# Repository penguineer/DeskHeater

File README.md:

# Desk Heater

> Low-power heated desktop for reducing conductive heat loss while working in a cool room.

This project adds a thin 24 V carbon heating film underneath a bamboo desktop. The goal is not to make the desk feel hot, but to keep the work surface close enough to room/body-neutral temperature that it no longer cools hands and forearms during long work sessions in winter.

The controller is based on an ESP8266 (ESP-12E) and provides:

- temperature monitoring with multiple NTC sensors
- hardware over-temperature protection independent of the ESP
- current, voltage, power and energy measurement
- slow duty-cycle control of the approximately 60 W heating film
- UART and Wi-Fi connectivity for monitoring and future controls

The KiCad design for the controller is in [`Controller/`](Controller/).

## Status

Work in progress. The electrical and mechanical design is currently being prototyped and characterized.

## License

This work is licensed under a [Creative Commons Attribution-ShareAlike 4.0 International License](http://creativecommons.org/licenses/by-sa/4.0/).

BY: Stefan Haun (mail@tuxathome.de)

See [LICENSE.txt](LICENSE.txt) for details.

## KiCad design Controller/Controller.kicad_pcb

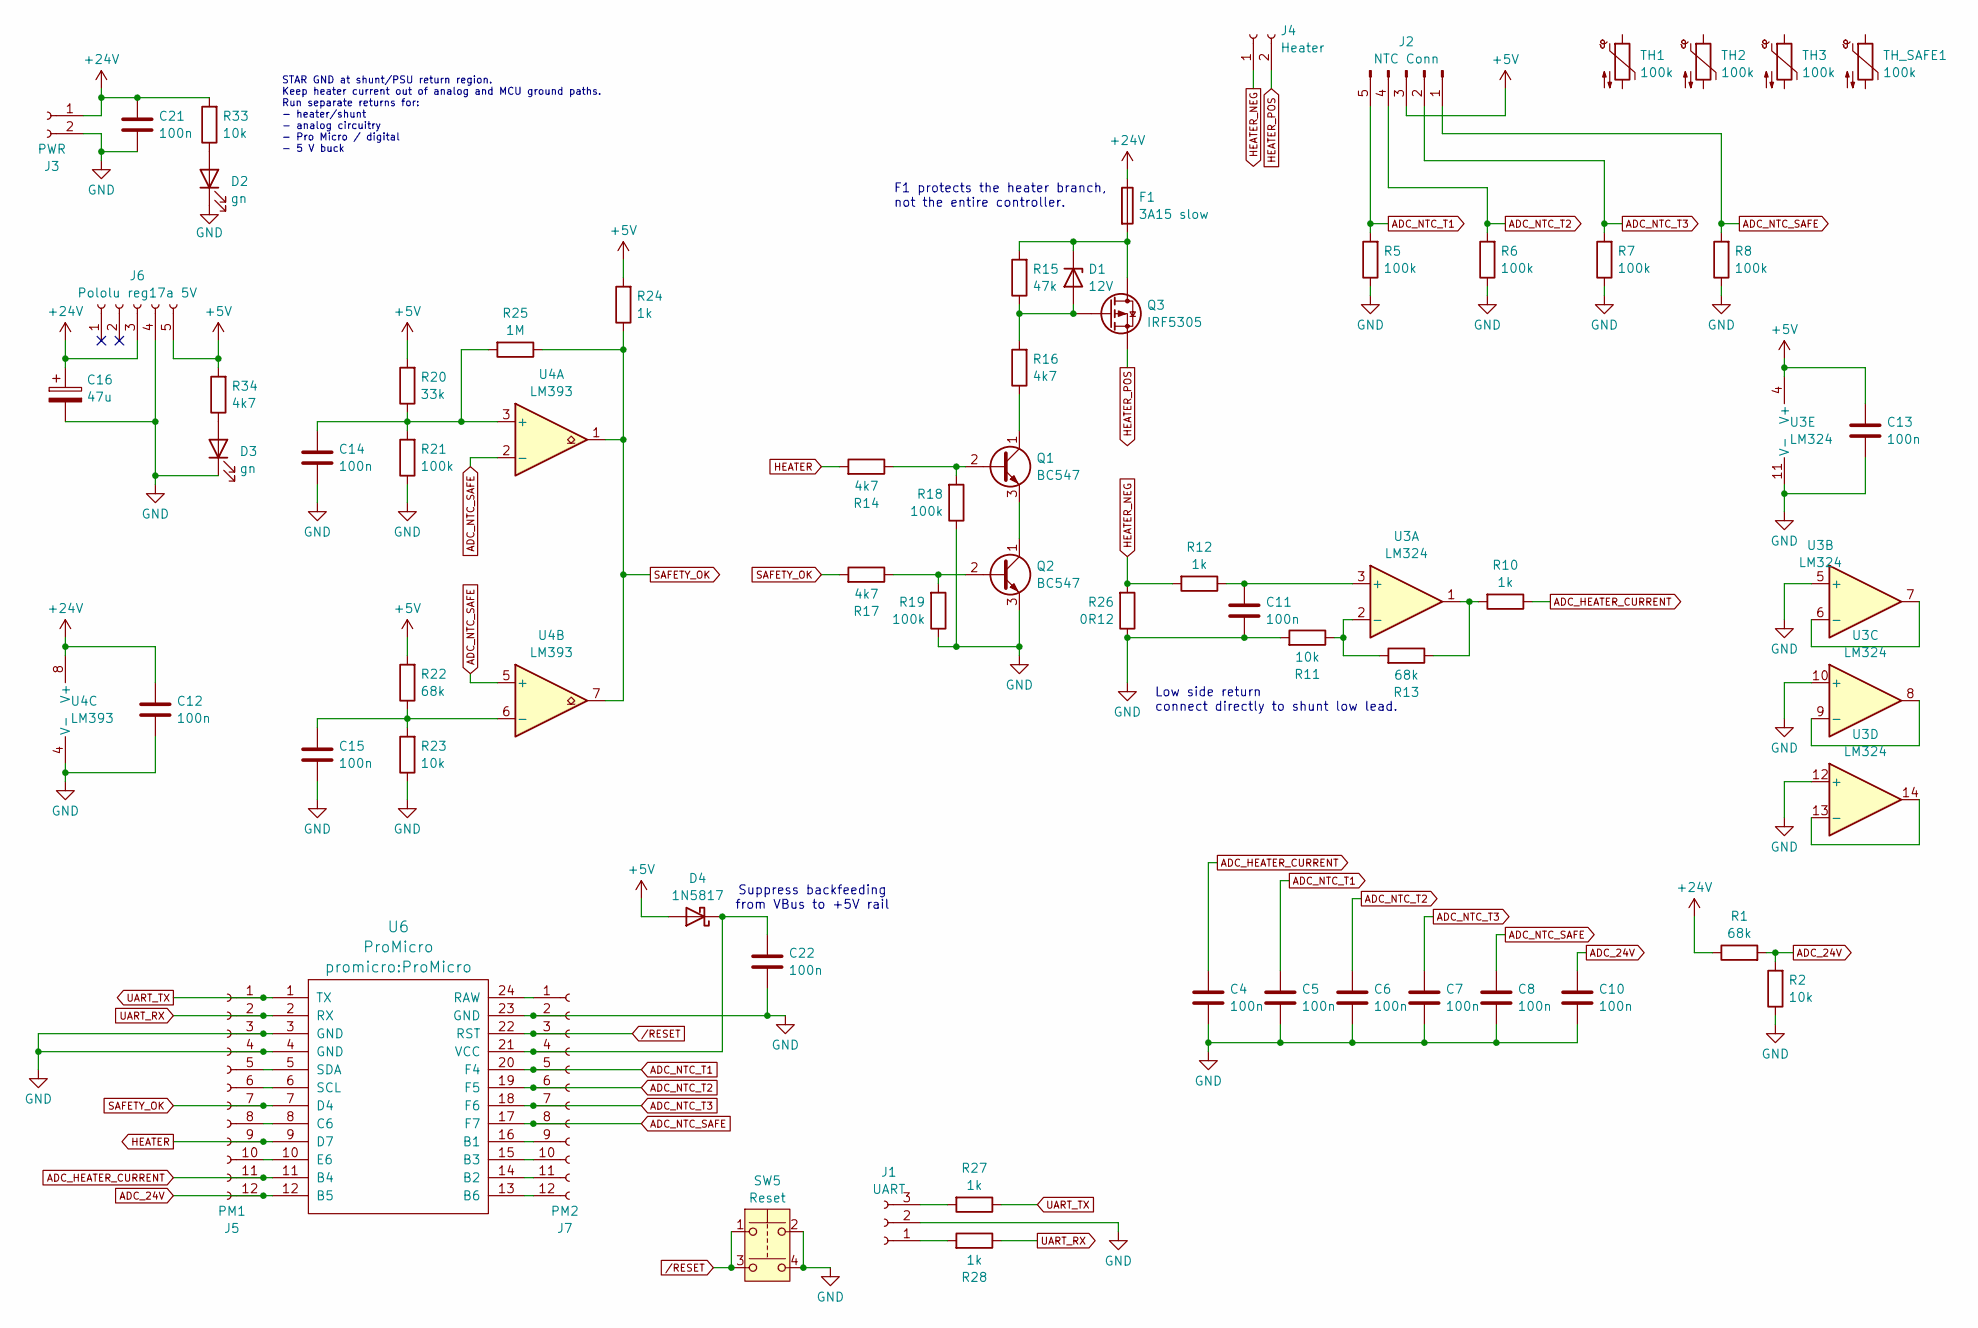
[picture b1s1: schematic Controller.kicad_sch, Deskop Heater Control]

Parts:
C4, C5, C6, C7, C8, C10, C11, C12, C13, C14, C15, C21, C22: 100n; C_Disc_D4.3mm_W1.9mm_P5.00mm
C16: 47u; CP_Radial_D6.3mm_P2.50mm
D1: 12V; D_DO-41_SOD81_P7.62mm_Horizontal
D2, D3: gn; LED_D3.0mm
D4: 1N5817; D_DO-41_SOD81_P10.16mm_Horizontal
F1: 3A15 slow; Fuseholder_Cylinder-5x20mm_Stelvio-Kontek_PTF78_Horizontal_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
J1: UART; PinHeader_1x03_P2.54mm_Vertical
J2: NTC Conn; JST_EH_B5B-EH-A_1x05_P2.50mm_Vertical
J3: PWR; JST_NV_B02P-NV_1x02_P5.00mm_Vertical
J4: Heater; JST_NV_B02P-NV_1x02_P5.00mm_Vertical
J5: PM1; PinSocket_1x12_P2.54mm_Vertical
J6: Pololu reg17a 5V; PinHeader_1x05_P2.54mm_Vertical
J7: PM2; PinSocket_1x12_P2.54mm_Vertical
Q1, Q2: BC547; TO-92_Inline
Q3: IRF5305; TO-220-3_Vertical
R1, R13, R22: 68k; R_Axial_DIN0207_L6.3mm_D2.5mm_P7.62mm_Horizontal
R2, R11, R23, R33: 10k; R_Axial_DIN0207_L6.3mm_D2.5mm_P7.62mm_Horizontal
R5, R6, R7, R8, R18, R19, R21: 100k; R_Axial_DIN0207_L6.3mm_D2.5mm_P7.62mm_Horizontal
R10, R12, R24, R27, R28: 1k; R_Axial_DIN0207_L6.3mm_D2.5mm_P7.62mm_Horizontal
R14, R16, R17, R34: 4k7; R_Axial_DIN0207_L6.3mm_D2.5mm_P7.62mm_Horizontal
R15: 47k; R_Axial_DIN0207_L6.3mm_D2.5mm_P7.62mm_Horizontal
R20: 33k; R_Axial_DIN0207_L6.3mm_D2.5mm_P7.62mm_Horizontal
R25: 1M; R_Axial_DIN0207_L6.3mm_D2.5mm_P7.62mm_Horizontal
R26: 0R12; R_Axial_DIN0614_L14.3mm_D5.7mm_P15.24mm_Horizontal
SW5: Reset; SW_DIP_SPSTx02_Slide_6.7x6.64mm_W7.62mm_P2.54mm_LowProfile
TH1, TH2, TH3: 100k; LQFP-100_14x14mm_P0.5mm
TH_SAFE1: 100k; LQFP-100_14x14mm_P0.5mm
U3: LM324; DIP-14_W7.62mm_LongPads
U4: LM393; DIP-8_W7.62mm_LongPads
U6: ProMicro

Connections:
+5V: C13.1, D4.2 (A), J2.3, J6.5, R20.2, R22.2, R24.2, R34.2, U3.4 (V+)
+24V: C12.1, C16.1, C21.1, F1.1, J3.1, J6.3, R1.1, R33.2, U4.8 (V+)
ADC_24V: C10.1, J5.12, R1.2, R2.2, U6.12 (B5)
ADC_HEATER_CURRENT: C4.1, J5.11, R10.1, U6.11 (B4)
ADC_NTC_SAFE: C8.1, J2.1, J7.8, R8.2, U4.2 (-), U4.5 (+), U6.17 (F7)
ADC_NTC_T1: C5.1, J2.5, J7.5, R5.2, U6.20 (F4)
ADC_NTC_T2: C6.1, J2.4, J7.6, R6.2, U6.19 (F5)
ADC_NTC_T3: C7.1, J2.2, J7.7, R7.2, U6.18 (F6)
GND: C4.2, C5.2, C6.2, C7.2, C8.2, C10.2, C11.2, C12.2, C13.2, C14.2, C15.2, C16.2, C21.2, C22.2, D2.1 (K), D3.1 (K), J1.2, J3.2, J5.3, J5.4, J6.4, J7.2, Q2.3 (E), R2.1, R5.1, R6.1, R7.1, R8.1, R11.2, R18.1, R19.1, R21.1, R23.1, R26.1, SW5.2, SW5.4, U3.5 (+), U3.10 (+), U3.11 (V-), U3.12 (+), U4.4 (V-), U6.3 (GND), U6.4 (GND), U6.23 (GND)
HEATER: J5.9, R14.2, U6.9 (D7)
HEATER_NEG: J4.1, R12.2, R26.2
HEATER_POS: J4.2, Q3.3 (S)
unnamed: D1.2 (A), Q3.1 (G), R15.1, R16.2
unnamed: D1.1 (K), F1.2, Q3.2 (D), R15.2
unnamed: D2.2 (A), R33.1
unnamed: D3.2 (A), R34.1
unnamed: C22.1, D4.1 (K), J7.4, U6.21 (VCC)
unnamed: J1.1, R28.2
unnamed: J1.3, R27.2
unnamed: J5.5, U6.5 (SDA)
unnamed: J5.6, U6.6 (SCL)
unnamed: J5.8, U6.8 (C6)
unnamed: J5.10, U6.10 (E6)
unnamed: J7.1, U6.24 (RAW)
unnamed: J7.9, U6.16 (B1)
unnamed: J7.10, U6.15 (B3)
unnamed: J7.11, U6.14 (B2)
unnamed: J7.12, U6.13 (B6)
unnamed: Q1.2 (B), R14.1, R18.2
unnamed: Q1.1 (C), R16.1
unnamed: Q1.3 (E), Q2.1 (C)
unnamed: Q2.2 (B), R17.1, R19.2
unnamed: R10.2, R13.1, U3.1
unnamed: C11.1, R12.1, U3.3 (+)
unnamed: R11.1, R13.2, U3.2 (-)
unnamed: U3.6 (-), U3.7
unnamed: U3.8, U3.9 (-)
unnamed: U3.13 (-), U3.14
unnamed: C14.1, R20.1, R21.2, R25.2, U4.3 (+)
unnamed: C15.1, R22.1, R23.2, U4.6 (-)
SAFETY_OK: J5.7, R17.2, R24.1, R25.1, U4.1, U4.7, U6.7 (D4)
UART_RX: J5.2, R28.1, U6.2 (RX)
UART_TX: J5.1, R27.1, U6.1 (TX)
/RESET: J7.3, SW5.1, SW5.3, U6.22 (RST)

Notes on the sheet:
Low side return connect directly to shunt low lead.
Suppress backfeeding from VBus to +5V rail
STAR GND at shunt/PSU return region. Keep heater current out of analog and MCU ground paths. Run separate returns for: - heater/shunt - analog circuitry - Pro Micro / digital - 5 V buck
F1 protects the heater branch, not the entire controller.

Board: 2 copper layers, 59 parts (0 on the bottom side), 35 nets, no tracks yet.
